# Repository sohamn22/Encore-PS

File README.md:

# Encore-PS

Input Voltage and Output Voltage Plots:

Input Power, Output Power, Input Current and Output Current Plots:

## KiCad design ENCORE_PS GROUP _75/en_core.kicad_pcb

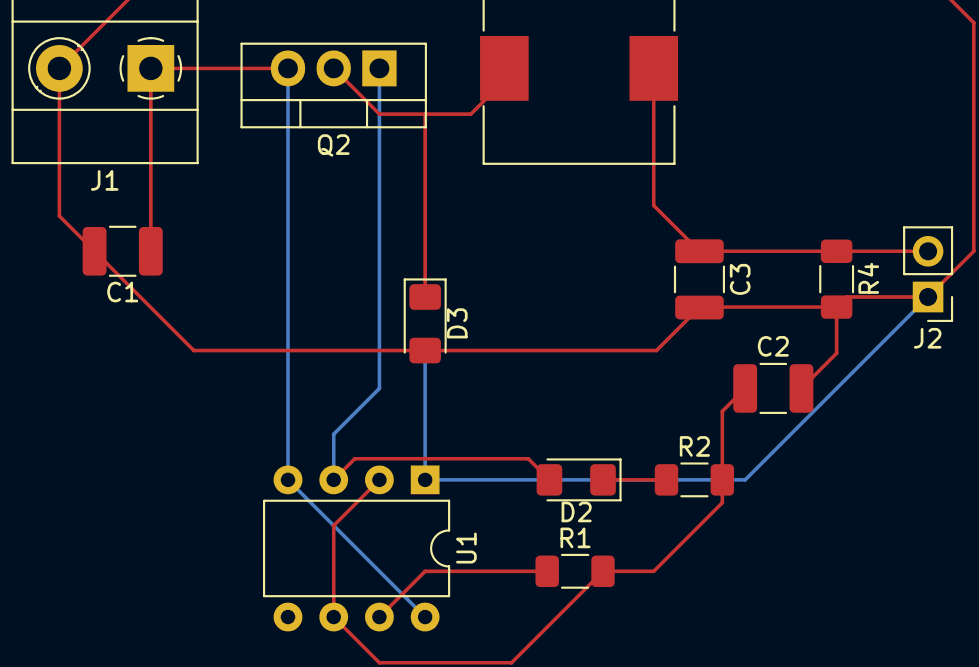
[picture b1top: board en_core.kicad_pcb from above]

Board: 2 copper layers, 13 parts (0 on the bottom side), 8 nets.

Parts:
C1: 22uF; C_1210_3225Metric_Pad1.33x2.70mm_HandSolder
C2: 1nF; C_1210_3225Metric_Pad1.33x2.70mm_HandSolder
C3: 150uF; C_1210_3225Metric_Pad1.33x2.70mm_HandSolder
D2: 1N4148; D_1206_3216Metric_Pad1.42x1.75mm_HandSolder
D3: RBR5LAM60A; D_1206_3216Metric_Pad1.42x1.75mm_HandSolder
J1: Input Source; TerminalBlock_Phoenix_MKDS-1,5-2-5.08_1x02_P5.08mm_Horizont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
J2: Output source; PinHeader_1x02_P2.54mm_Vertical
L1: 100uH; L_10.4x10.4_H4.8
Q2: IRFZ44N; TO-220-3_Vertical
R1: 27k; R_1206_3216Metric_Pad1.30x1.75mm_HandSolder
R2: 3.3k; R_1206_3216Metric_Pad1.30x1.75mm_HandSolder
R4: Rl; R_1206_3216Metric_Pad1.30x1.75mm_HandSolder
U1: NE555P; DIP-8_W7.62mm

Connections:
47k Hz CLK SRC: D2.2 (A), Q2.1 (G), U1.3 (Q)
GND: C1.2, C2.2, C3.2, D3.2 (A), J1.2, J2.1, R4.2, U1.1 (GND)
unnamed: D2.1 (K), R2.1
unnamed: D3.1 (K), L1.1, Q2.2 (D)
unnamed: R1.1, U1.7 (DIS)
unnamed: C2.1, R1.2, R2.2, U1.2 (TR), U1.6 (THR)
Vin: C1.1, J1.1, Q2.3 (S), U1.4 (R), U1.8 (VCC)
Vo: C3.1, J2.2, L1.2, R4.1
